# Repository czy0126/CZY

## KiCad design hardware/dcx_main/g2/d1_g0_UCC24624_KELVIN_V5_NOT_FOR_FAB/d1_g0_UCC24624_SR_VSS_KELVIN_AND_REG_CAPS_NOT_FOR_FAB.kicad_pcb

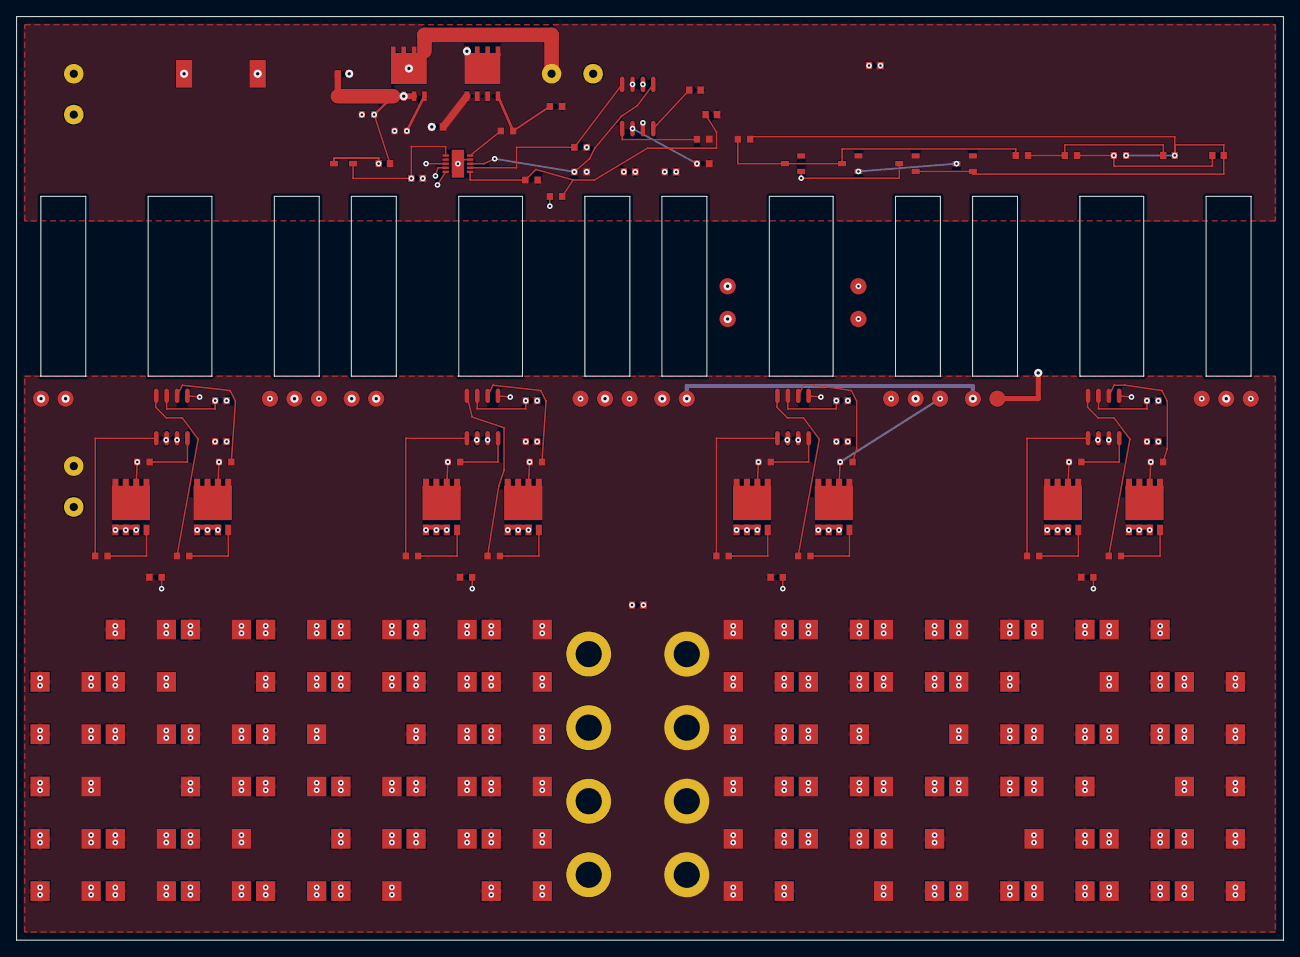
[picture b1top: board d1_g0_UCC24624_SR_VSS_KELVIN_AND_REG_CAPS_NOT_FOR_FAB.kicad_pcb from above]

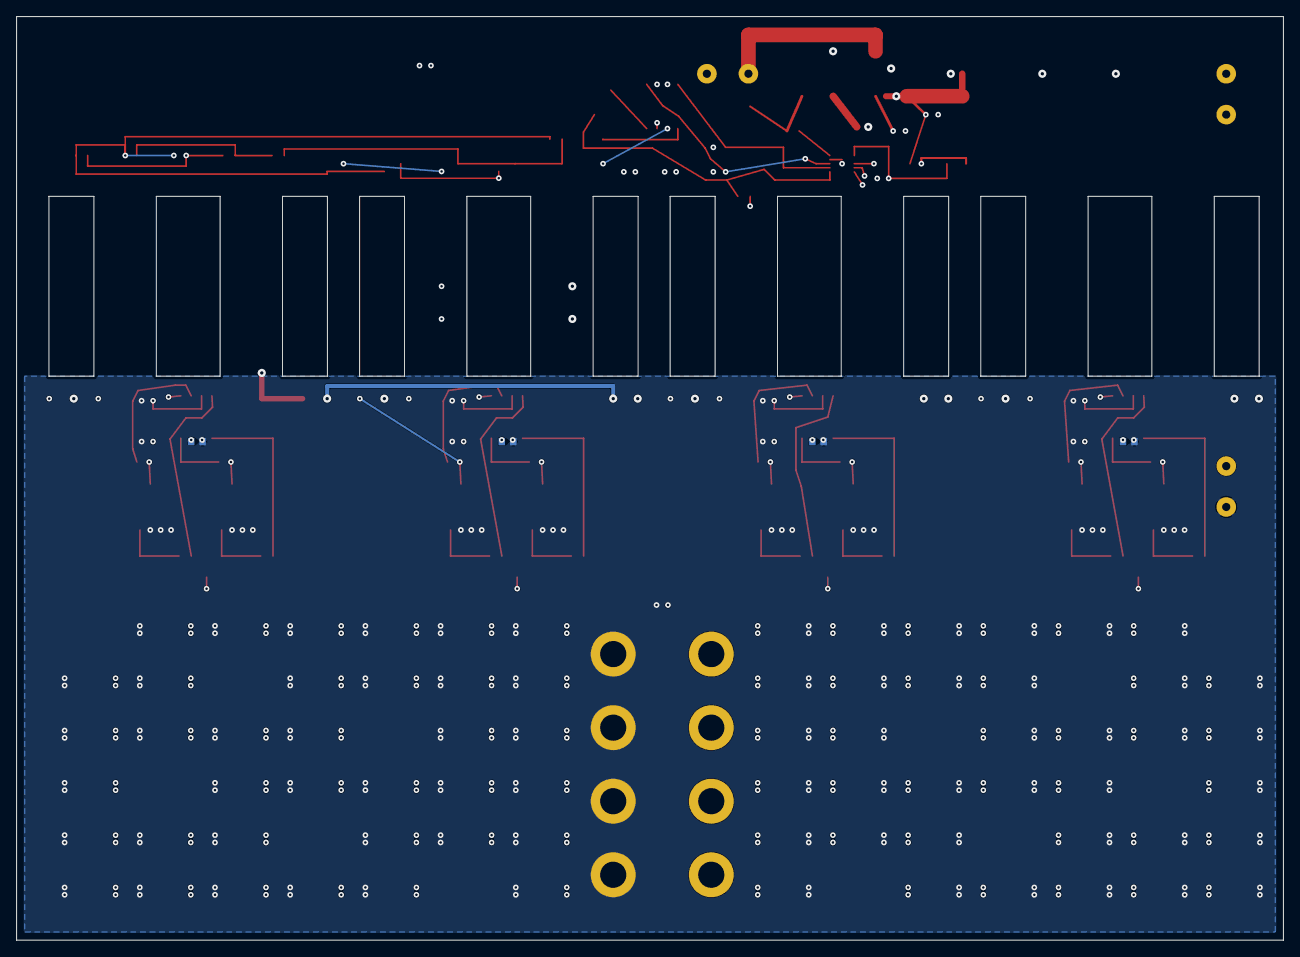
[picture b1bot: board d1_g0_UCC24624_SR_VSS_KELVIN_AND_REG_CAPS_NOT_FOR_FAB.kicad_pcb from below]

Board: 12 copper layers, 155.0 x 113.0 mm, 161 parts (4 on the bottom side), 70 nets.

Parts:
C5, C6, C11, C12, C13, C101, C102, C103, C104, C105, C106, C107, C108, C109, C110, C111, C112: V15_PROVISIONAL_CAD_ONLY
C7, C8, C9, C10: GRM188C71E225KE11_2u2_25V_X7S_DC_BIAS_REVIEW
CHB01, CHB02, CHB03, CHB04, CHB05, CHB06, CHB07, CHB08, CHB09, CHB10, CHB11, CHB12, CHB13, CHB14, CHB15, CHB16, CHB17, CHB18, CHB19, CHB20, CHB21, CHB22, CHB23, CHB24, CHB25, CHB26, CHB27, CHB28, CHB29, CHB30, CHB31, CHB32, CHB33, CHB34, CHB35, CHB36, CHB37, CHB38, CHB39, CHB40, CHB41, CHB42, CHB43, CHB44, CHB45, CHB46, CHB47, CHB48, CHB49, CHB50, CHB51, CHB52, CHB53, CHB54, CHB55, CHB56, CHB57, CHB58, CHB59, CHB60, CHB61, CHB62, CHB63, CHB64, CHB65, CHB66, CHB67, CHB68, CHB69, CHB70, CHB71, CHB72: T530X477M006ATE004; KEMET_T530X_7343_43_OEM_B
CT: LOGICAL_4LAND_CT_NOT_VENDOR_PINOUT
Cin: V15_PROVISIONAL_CAD_ONLY
Cout: V15_PROVISIONAL_CAD_ONLY
Cr: V15_PROVISIONAL_CAD_ONLY
D_BT: V15_PROVISIONAL_CAD_ONLY
D_CT1, D_CT2, D_CT3, D_CT4: V15_PROVISIONAL_CAD_ONLY
J_BIAS_P: PRIMARY_EXTERNAL_12V_NOT_BUILT
J_BIAS_S: SECONDARY_ISOLATED_EXTERNAL_12V_NOT_BUILT
J_IN: V15_PROVISIONAL_CAD_ONLY
J_OUT: EIGHT_PLATED_CONTACTS_VENDOR_UNRATED_NOT_FOR_FAB
Lr: V15_PROVISIONAL_CAD_ONLY
QH: V15_PROVISIONAL_CAD_ONLY
QL: V15_PROVISIONAL_CAD_ONLY
R1, R2, R3, R4, R5, R7, R9, R10, R15, R16, R17, R18, R19, R20, R21, R22, R23, R24, R25, R26, R27, R28, R29, R30, R31, R32, R33, R34, R35: V15_PROVISIONAL_CAD_ONLY
R8: 1k_DNP_UNTIL_EXTERNAL_PERMIT_TESTED
RK1, RK2, RK3, RK4: RC0603JR-070RL_0R_SR_KELVIN_DFM_UNAPPROVED
SR1A, SR1B, SR2A, SR2B, SR3A, SR3B, SR4A, SR4B: V15_PROVISIONAL_CAD_ONLY
T1, T2, T3, T4: LOGICAL_5LAND_NOT_VENDOR_PINOUT_NOT_FOR_FAB
U1, U2, U3, U4, U5, U6: V15_PROVISIONAL_CAD_ONLY

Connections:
CR_CT: CT.PRI_A, Cr.2
CS1: CT.SEC_A, D_CT1.1, D_CT3.3
CS2: CT.SEC_B, D_CT2.1, D_CT4.3
CT_LR: CT.PRI_B, Lr.1
DT: R1.1, U1.1
GA1: R20.2, SR1A.4
GA2: R22.2, SR2A.4
GA3: R24.2, SR3A.4
GA4: R26.2, SR4A.4
GB1: R21.2, SR1B.4
GB2: R23.2, SR2B.4
GB3: R25.2, SR3B.4
GB4: R27.2, SR4B.4
GD1: R9.1, U1.8, U2.7
GD2: R10.1, U1.5, U2.8
GH: QH.4, R4.2, R18.1
GH_DRV: R4.1, U2.4
GL: QL.4, R5.2, R19.1
GL_DRV: R5.1, U2.10
HB: C5.1, D_BT.1, U2.3
OC: C12.1, R16.2, R17.1, U1.3
OC1: C11.1, R15.2, R16.1
OCD: D_CT1.3, D_CT2.3, R3.1, R15.1
OCM: C11.2, C12.2, D_CT3.1, D_CT4.1, R3.2, R17.2
PGND: C6.2, C13.2, C101.2, C102.2, C103.2, C104.2, Cin.2, J_BIAS_P.2, J_IN.2, QL.1, QL.2, QL.3, R1.2, R2.2, R7.2, R9.2, R10.2, R19.2, T4.PRI_B, U1.6, U2.9, U2.11
PRI_12: T1.PRI_B, T2.PRI_A
PRI_23: T2.PRI_B, T3.PRI_A
PRI_34: T3.PRI_B, T4.PRI_A
PRI_T1: Lr.2, T1.PRI_A
REG1: C7.1, U3.3
REG2: C8.1, U4.3
REG3: C9.1, U5.3
REG4: C10.1, U6.3
RT: R2.1, U1.2
RUN: C13.1, R7.1, R8.2, U2.6
SEC1_A: R28.1, SR1A.5, SR1A.6, SR1A.7, SR1A.8, T1.SEC_A
SEC1_B: R29.1, SR1B.5, SR1B.6, SR1B.7, SR1B.8, T1.SEC_B
SEC2_A: R30.1, SR2A.5, SR2A.6, SR2A.7, SR2A.8, T2.SEC_A
SEC2_B: R31.1, SR2B.5, SR2B.6, SR2B.7, SR2B.8, T2.SEC_B
SEC3_A: R32.1, SR3A.5, SR3A.6, SR3A.7, SR3A.8, T3.SEC_A
SEC3_B: R33.1, SR3B.5, SR3B.6, SR3B.7, SR3B.8, T3.SEC_B
SEC4_A: R34.1, SR4A.5, SR4A.6, SR4A.7, SR4A.8, T4.SEC_A
SEC4_B: R35.1, SR4B.5, SR4B.6, SR4B.7, SR4B.8, T4.SEC_B
SR_KELVIN_1: RK1.2, U3.5
SR_KELVIN_2: RK2.2, U4.5
SR_KELVIN_3: RK3.2, U5.5
SR_KELVIN_4: RK4.2, U6.5
SR_SOURCE_RETURN: C7.2, C8.2, C9.2, C10.2, C105.2, C106.2, C107.2, C108.2, C109.2, C110.2, C111.2, C112.2, CHB01.2, CHB02.2, CHB03.2, CHB04.2, CHB05.2, CHB06.2, CHB07.2, CHB08.2, CHB09.2, CHB10.2, CHB11.2, CHB12.2, CHB13.2, CHB14.2, CHB15.2, CHB16.2, CHB17.2, CHB18.2, CHB19.2, CHB20.2, CHB21.2, CHB22.2, CHB23.2, CHB24.2, CHB25.2, CHB26.2, CHB27.2, CHB28.2, CHB29.2, CHB30.2, CHB31.2, CHB32.2, CHB33.2, CHB34.2, CHB35.2, CHB36.2, CHB37.2, CHB38.2, CHB39.2, CHB40.2, CHB41.2, CHB42.2, CHB43.2, CHB44.2, CHB45.2, CHB46.2, CHB47.2, CHB48.2, CHB49.2, CHB50.2, CHB51.2, CHB52.2, CHB53.2, CHB54.2, CHB55.2, CHB56.2, CHB57.2, CHB58.2, CHB59.2, CHB60.2, CHB61.2, CHB62.2, CHB63.2, CHB64.2, CHB65.2, CHB66.2, CHB67.2, CHB68.2, CHB69.2, CHB70.2, CHB71.2, CHB72.2, Cout.2, J_BIAS_S.2, J_OUT.2, RK1.1, RK2.1, RK3.1, RK4.1, SR1A.1, SR1A.2, SR1A.3, SR1B.1, SR1B.2, SR1B.3, SR2A.1, SR2A.2, SR2A.3, SR2B.1, SR2B.2, SR2B.3, SR3A.1, SR3A.2, SR3A.3, SR3B.1, SR3B.2, SR3B.3, SR4A.1, SR4A.2, SR4A.3, SR4B.1, SR4B.2, SR4B.3, U3.2, U4.2, U5.2, U6.2
SS: C6.1, U1.4
SW: C5.2, Cr.1, QH.1, QH.2, QH.3, QL.5, QL.6, QL.7, QL.8, QL.9, R18.2, U2.5
VCC12: C101.1, C102.1, C103.1, C104.1, D_BT.2, J_BIAS_P.1, R8.1, U1.7, U2.1
VCC12_S: C105.1, C106.1, C107.1, C108.1, C109.1, C110.1, C111.1, C112.1, J_BIAS_S.1, U3.7, U4.7, U5.7, U6.7
VD1_A: R28.2, U3.4
VD1_B: R29.2, U3.6
VD2_A: R30.2, U4.4
VD2_B: R31.2, U4.6
VD3_A: R32.2, U5.4
VD3_B: R33.2, U5.6
VD4_A: R34.2, U6.4
VD4_B: R35.2, U6.6
VG1_A: R20.1, U3.1
VG1_B: R21.1, U3.8
VG2_A: R22.1, U4.1
VG2_B: R23.1, U4.8
VG3_A: R24.1, U5.1
VG3_B: R25.1, U5.8
VG4_A: R26.1, U6.1
VG4_B: R27.1, U6.8
VIN_P: Cin.1, J_IN.1, QH.5, QH.6, QH.7, QH.8, QH.9
VOUT: CHB01.1, CHB02.1, CHB03.1, CHB04.1, CHB05.1, CHB06.1, CHB07.1, CHB08.1, CHB09.1, CHB10.1, CHB11.1, CHB12.1, CHB13.1, CHB14.1, CHB15.1, CHB16.1, CHB17.1, CHB18.1, CHB19.1, CHB20.1, CHB21.1, CHB22.1, CHB23.1, CHB24.1, CHB25.1, CHB26.1, CHB27.1, CHB28.1, CHB29.1, CHB30.1, CHB31.1, CHB32.1, CHB33.1, CHB34.1, CHB35.1, CHB36.1, CHB37.1, CHB38.1, CHB39.1, CHB40.1, CHB41.1, CHB42.1, CHB43.1, CHB44.1, CHB45.1, CHB46.1, CHB47.1, CHB48.1, CHB49.1, CHB50.1, CHB51.1, CHB52.1, CHB53.1, CHB54.1, CHB55.1, CHB56.1, CHB57.1, CHB58.1, CHB59.1, CHB60.1, CHB61.1, CHB62.1, CHB63.1, CHB64.1, CHB65.1, CHB66.1, CHB67.1, CHB68.1, CHB69.1, CHB70.1, CHB71.1, CHB72.1, Cout.1, J_OUT.1, T1.CTAP, T2.CTAP, T3.CTAP, T4.CTAP

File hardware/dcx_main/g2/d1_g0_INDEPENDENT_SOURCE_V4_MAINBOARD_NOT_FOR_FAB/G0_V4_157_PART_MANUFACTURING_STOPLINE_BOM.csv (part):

Designator,DesignIntentMPN_VENDOR_UNVERIFIED,DNP,NativeTrialValue,NativePadObjects,NativeRefPinNet,QualifiedPCBFootprint,RealMagneticPinDotSigned
C10,C0603_100n,no,V15_PROVISIONAL_CAD_ONLY,2,1=REG4;2=SR_SOURCE_RETURN,no,no
C101,C0603_100n (design value from peripheral register; OEM not qualified),no,V15_PROVISIONAL_CAD_ONLY,2,1=VCC12;2=PGND,no,no
C102,C0603_100n (design value from peripheral register; OEM not qualified),no,V15_PROVISIONAL_CAD_ONLY,2,1=VCC12;2=PGND,no,no
C103,C0603_100n (design value from peripheral register; OEM not qualified),no,V15_PROVISIONAL_CAD_ONLY,2,1=VCC12;2=PGND,no,no
C104,C0603_100n (design value from peripheral register; OEM not qualified),no,V15_PROVISIONAL_CAD_ONLY,2,1=VCC12;2=PGND,no,no
C105,C0603_100n (design value from peripheral register; OEM not qualified),no,V15_PROVISIONAL_CAD_ONLY,2,1=VCC12_S;2=SR_SOURCE_RETURN,no,no
C106,C0603_100n (design value from peripheral register; OEM not qualified),no,V15_PROVISIONAL_CAD_ONLY,2,1=VCC12_S;2=SR_SOURCE_RETURN,no,no
C107,C0603_100n (design value from peripheral register; OEM not qualified),no,V15_PROVISIONAL_CAD_ONLY,2,1=VCC12_S;2=SR_SOURCE_RETURN,no,no
C108,C0603_100n (design value from peripheral register; OEM not qualified),no,V15_PROVISIONAL_CAD_ONLY,2,1=VCC12_S;2=SR_SOURCE_RETURN,no,no
C109,C0603_100n (design value from peripheral register; OEM not qualified),no,V15_PROVISIONAL_CAD_ONLY,2,1=VCC12_S;2=SR_SOURCE_RETURN,no,no
C11,C0603_100n,no,V15_PROVISIONAL_CAD_ONLY,2,1=OC1;2=OCM,no,no
C110,C0603_100n (design value from peripheral register; OEM not qualified),no,V15_PROVISIONAL_CAD_ONLY,2,1=VCC12_S;2=SR_SOURCE_RETURN,no,no
C111,C0603_100n (design value from peripheral register; OEM not qualified),no,V15_PROVISIONAL_CAD_ONLY,2,1=VCC12_S;2=SR_SOURCE_RETURN,no,no
C112,C0603_100n (design value from peripheral register; OEM not qualified),no,V15_PROVISIONAL_CAD_ONLY,2,1=VCC12_S;2=SR_SOURCE_RETURN,no,no
C12,C0603_100n,no,V15_PROVISIONAL_CAD_ONLY,2,1=OC;2=OCM,no,no
C13,C0603_100n (design value from peripheral register; OEM not qualified),no,V15_PROVISIONAL_CAD_ONLY,2,1=RUN;2=PGND,no,no
C5,C0603_100n,no,V15_PROVISIONAL_CAD_ONLY,2,1=HB;2=SW,no,no
C6,C0603_100n,no,V15_PROVISIONAL_CAD_ONLY,2,1=SS;2=PGND,no,no
C7,C0603_100n,no,V15_PROVISIONAL_CAD_ONLY,2,1=REG1;2=SR_SOURCE_RETURN,no,no
C8,C0603_100n,no,V15_PROVISIONAL_CAD_ONLY,2,1=REG2;2=SR_SOURCE_RETURN,no,no
C9,C0603_100n,no,V15_PROVISIONAL_CAD_ONLY,2,1=REG3;2=SR_SOURCE_RETURN,no,no
CHB01,"T530 OEM tentative, MPN and derating require signoff",no,T530X477M006ATE004,2,1=VOUT;2=SR_SOURCE_RETURN,no,no
CHB02,"T530 OEM tentative, MPN and derating require signoff",no,T530X477M006ATE004,2,1=VOUT;2=SR_SOURCE_RETURN,no,no
CHB03,"T530 OEM tentative, MPN and derating require signoff",no,T530X477M006ATE004,2,1=VOUT;2=SR_SOURCE_RETURN,no,no
CHB04,"T530 OEM tentative, MPN and derating require signoff",no,T530X477M006ATE004,2,1=VOUT;2=SR_SOURCE_RETURN,no,no
CHB05,"T530 OEM tentative, MPN and derating require signoff",no,T530X477M006ATE004,2,1=VOUT;2=SR_SOURCE_RETURN,no,no
CHB06,"T530 OEM tentative, MPN and derating require signoff",no,T530X477M006ATE004,2,1=VOUT;2=SR_SOURCE_RETURN,no,no
CHB07,"T530 OEM tentative, MPN and derating require signoff",no,T530X477M006ATE004,2,1=VOUT;2=SR_SOURCE_RETURN,no,no
CHB08,"T530 OEM tentative, MPN and derating require signoff",no,T530X477M006ATE004,2,1=VOUT;2=SR_SOURCE_RETURN,no,no
CHB09,"T530 OEM tentative, MPN and derating require signoff",no,T530X477M006ATE004,2,1=VOUT;2=SR_SOURCE_RETURN,no,no
CHB10,"T530 OEM tentative, MPN and derating require signoff",no,T530X477M006ATE004,2,1=VOUT;2=SR_SOURCE_RETURN,no,no
CHB11,"T530 OEM tentative, MPN and derating require signoff",no,T530X477M006ATE004,2,1=VOUT;2=SR_SOURCE_RETURN,no,no
CHB12,"T530 OEM tentative, MPN and derating require signoff",no,T530X477M006ATE004,2,1=VOUT;2=SR_SOURCE_RETURN,no,no
CHB13,"T530 OEM tentative, MPN and derating require signoff",no,T530X477M006ATE004,2,1=VOUT;2=SR_SOURCE_RETURN,no,no
CHB14,"T530 OEM tentative, MPN and derating require signoff",no,T530X477M006ATE004,2,1=VOUT;2=SR_SOURCE_RETURN,no,no
CHB15,"T530 OEM tentative, MPN and derating require signoff",no,T530X477M006ATE004,2,1=VOUT;2=SR_SOURCE_RETURN,no,no
CHB16,"T530 OEM tentative, MPN and derating require signoff",no,T530X477M006ATE004,2,1=VOUT;2=SR_SOURCE_RETURN,no,no
CHB17,"T530 OEM tentative, MPN and derating require signoff",no,T530X477M006ATE004,2,1=VOUT;2=SR_SOURCE_RETURN,no,no
CHB18,"T530 OEM tentative, MPN and derating require signoff",no,T530X477M006ATE004,2,1=VOUT;2=SR_SOURCE_RETURN,no,no
CHB19,"T530 OEM tentative, MPN and derating require signoff",no,T530X477M006ATE004,2,1=VOUT;2=SR_SOURCE_RETURN,no,no
CHB20,"T530 OEM tentative, MPN and derating require signoff",no,T530X477M006ATE004,2,1=VOUT;2=SR_SOURCE_RETURN,no,no
CHB21,"T530 OEM tentative, MPN and derating require signoff",no,T530X477M006ATE004,2,1=VOUT;2=SR_SOURCE_RETURN,no,no
CHB22,"T530 OEM tentative, MPN and derating require signoff",no,T530X477M006ATE004,2,1=VOUT;2=SR_SOURCE_RETURN,no,no
CHB23,"T530 OEM tentative, MPN and derating require signoff",no,T530X477M006ATE004,2,1=VOUT;2=SR_SOURCE_RETURN,no,no
CHB24,"T530 OEM tentative, MPN and derating require signoff",no,T530X477M006ATE004,2,1=VOUT;2=SR_SOURCE_RETURN,no,no
CHB25,"T530 OEM tentative, MPN and derating require signoff",no,T530X477M006ATE004,2,1=VOUT;2=SR_SOURCE_RETURN,no,no
CHB26,"T530 OEM tentative, MPN and derating require signoff",no,T530X477M006ATE004,2,1=VOUT;2=SR_SOURCE_RETURN,no,no
CHB27,"T530 OEM tentative, MPN and derating require signoff",no,T530X477M006ATE004,2,1=VOUT;2=SR_SOURCE_RETURN,no,no
CHB28,"T530 OEM tentative, MPN and derating require signoff",no,T530X477M006ATE004,2,1=VOUT;2=SR_SOURCE_RETURN,no,no
CHB29,"T530 OEM tentative, MPN and derating require signoff",no,T530X477M006ATE004,2,1=VOUT;2=SR_SOURCE_RETURN,no,no
CHB30,"T530 OEM tentative, MPN and derating require signoff",no,T530X477M006ATE004,2,1=VOUT;2=SR_SOURCE_RETURN,no,no
CHB31,"T530 OEM tentative, MPN and derating require signoff",no,T530X477M006ATE004,2,1=VOUT;2=SR_SOURCE_RETURN,no,no
CHB32,"T530 OEM tentative, MPN and derating require signoff",no,T530X477M006ATE004,2,1=VOUT;2=SR_SOURCE_RETURN,no,no
CHB33,"T530 OEM tentative, MPN and derating require signoff",no,T530X477M006ATE004,2,1=VOUT;2=SR_SOURCE_RETURN,no,no
CHB34,"T530 OEM tentative, MPN and derating require signoff",no,T530X477M006ATE004,2,1=VOUT;2=SR_SOURCE_RETURN,no,no
CHB35,"T530 OEM tentative, MPN and derating require signoff",no,T530X477M006ATE004,2,1=VOUT;2=SR_SOURCE_RETURN,no,no
CHB36,"T530 OEM tentative, MPN and derating require signoff",no,T530X477M006ATE004,2,1=VOUT;2=SR_SOURCE_RETURN,no,no
CHB37,"T530 OEM tentative, MPN and derating require signoff",no,T530X477M006ATE004,2,1=VOUT;2=SR_SOURCE_RETURN,no,no
CHB38,"T530 OEM tentative, MPN and derating require signoff",no,T530X477M006ATE004,2,1=VOUT;2=SR_SOURCE_RETURN,no,no
CHB39,"T530 OEM tentative, MPN and derating require signoff",no,T530X477M006ATE004,2,1=VOUT;2=SR_SOURCE_RETURN,no,no
CHB40,"T530 OEM tentative, MPN and derating require signoff",no,T530X477M006ATE004,2,1=VOUT;2=SR_SOURCE_RETURN,no,no
CHB41,"T530 OEM tentative, MPN and derating require signoff",no,T530X477M006ATE004,2,1=VOUT;2=SR_SOURCE_RETURN,no,no
CHB42,"T530 OEM tentative, MPN and derating require signoff",no,T530X477M006ATE004,2,1=VOUT;2=SR_SOURCE_RETURN,no,no
CHB43,"T530 OEM tentative, MPN and derating require signoff",no,T530X477M006ATE004,2,1=VOUT;2=SR_SOURCE_RETURN,no,no
CHB44,"T530 OEM tentative, MPN and derating require signoff",no,T530X477M006ATE004,2,1=VOUT;2=SR_SOURCE_RETURN,no,no
CHB45,"T530 OEM tentative, MPN and derating require signoff",no,T530X477M006ATE004,2,1=VOUT;2=SR_SOURCE_RETURN,no,no
CHB46,"T530 OEM tentative, MPN and derating require signoff",no,T530X477M006ATE004,2,1=VOUT;2=SR_SOURCE_RETURN,no,no
CHB47,"T530 OEM tentative, MPN and derating require signoff",no,T530X477M006ATE004,2,1=VOUT;2=SR_SOURCE_RETURN,no,no
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
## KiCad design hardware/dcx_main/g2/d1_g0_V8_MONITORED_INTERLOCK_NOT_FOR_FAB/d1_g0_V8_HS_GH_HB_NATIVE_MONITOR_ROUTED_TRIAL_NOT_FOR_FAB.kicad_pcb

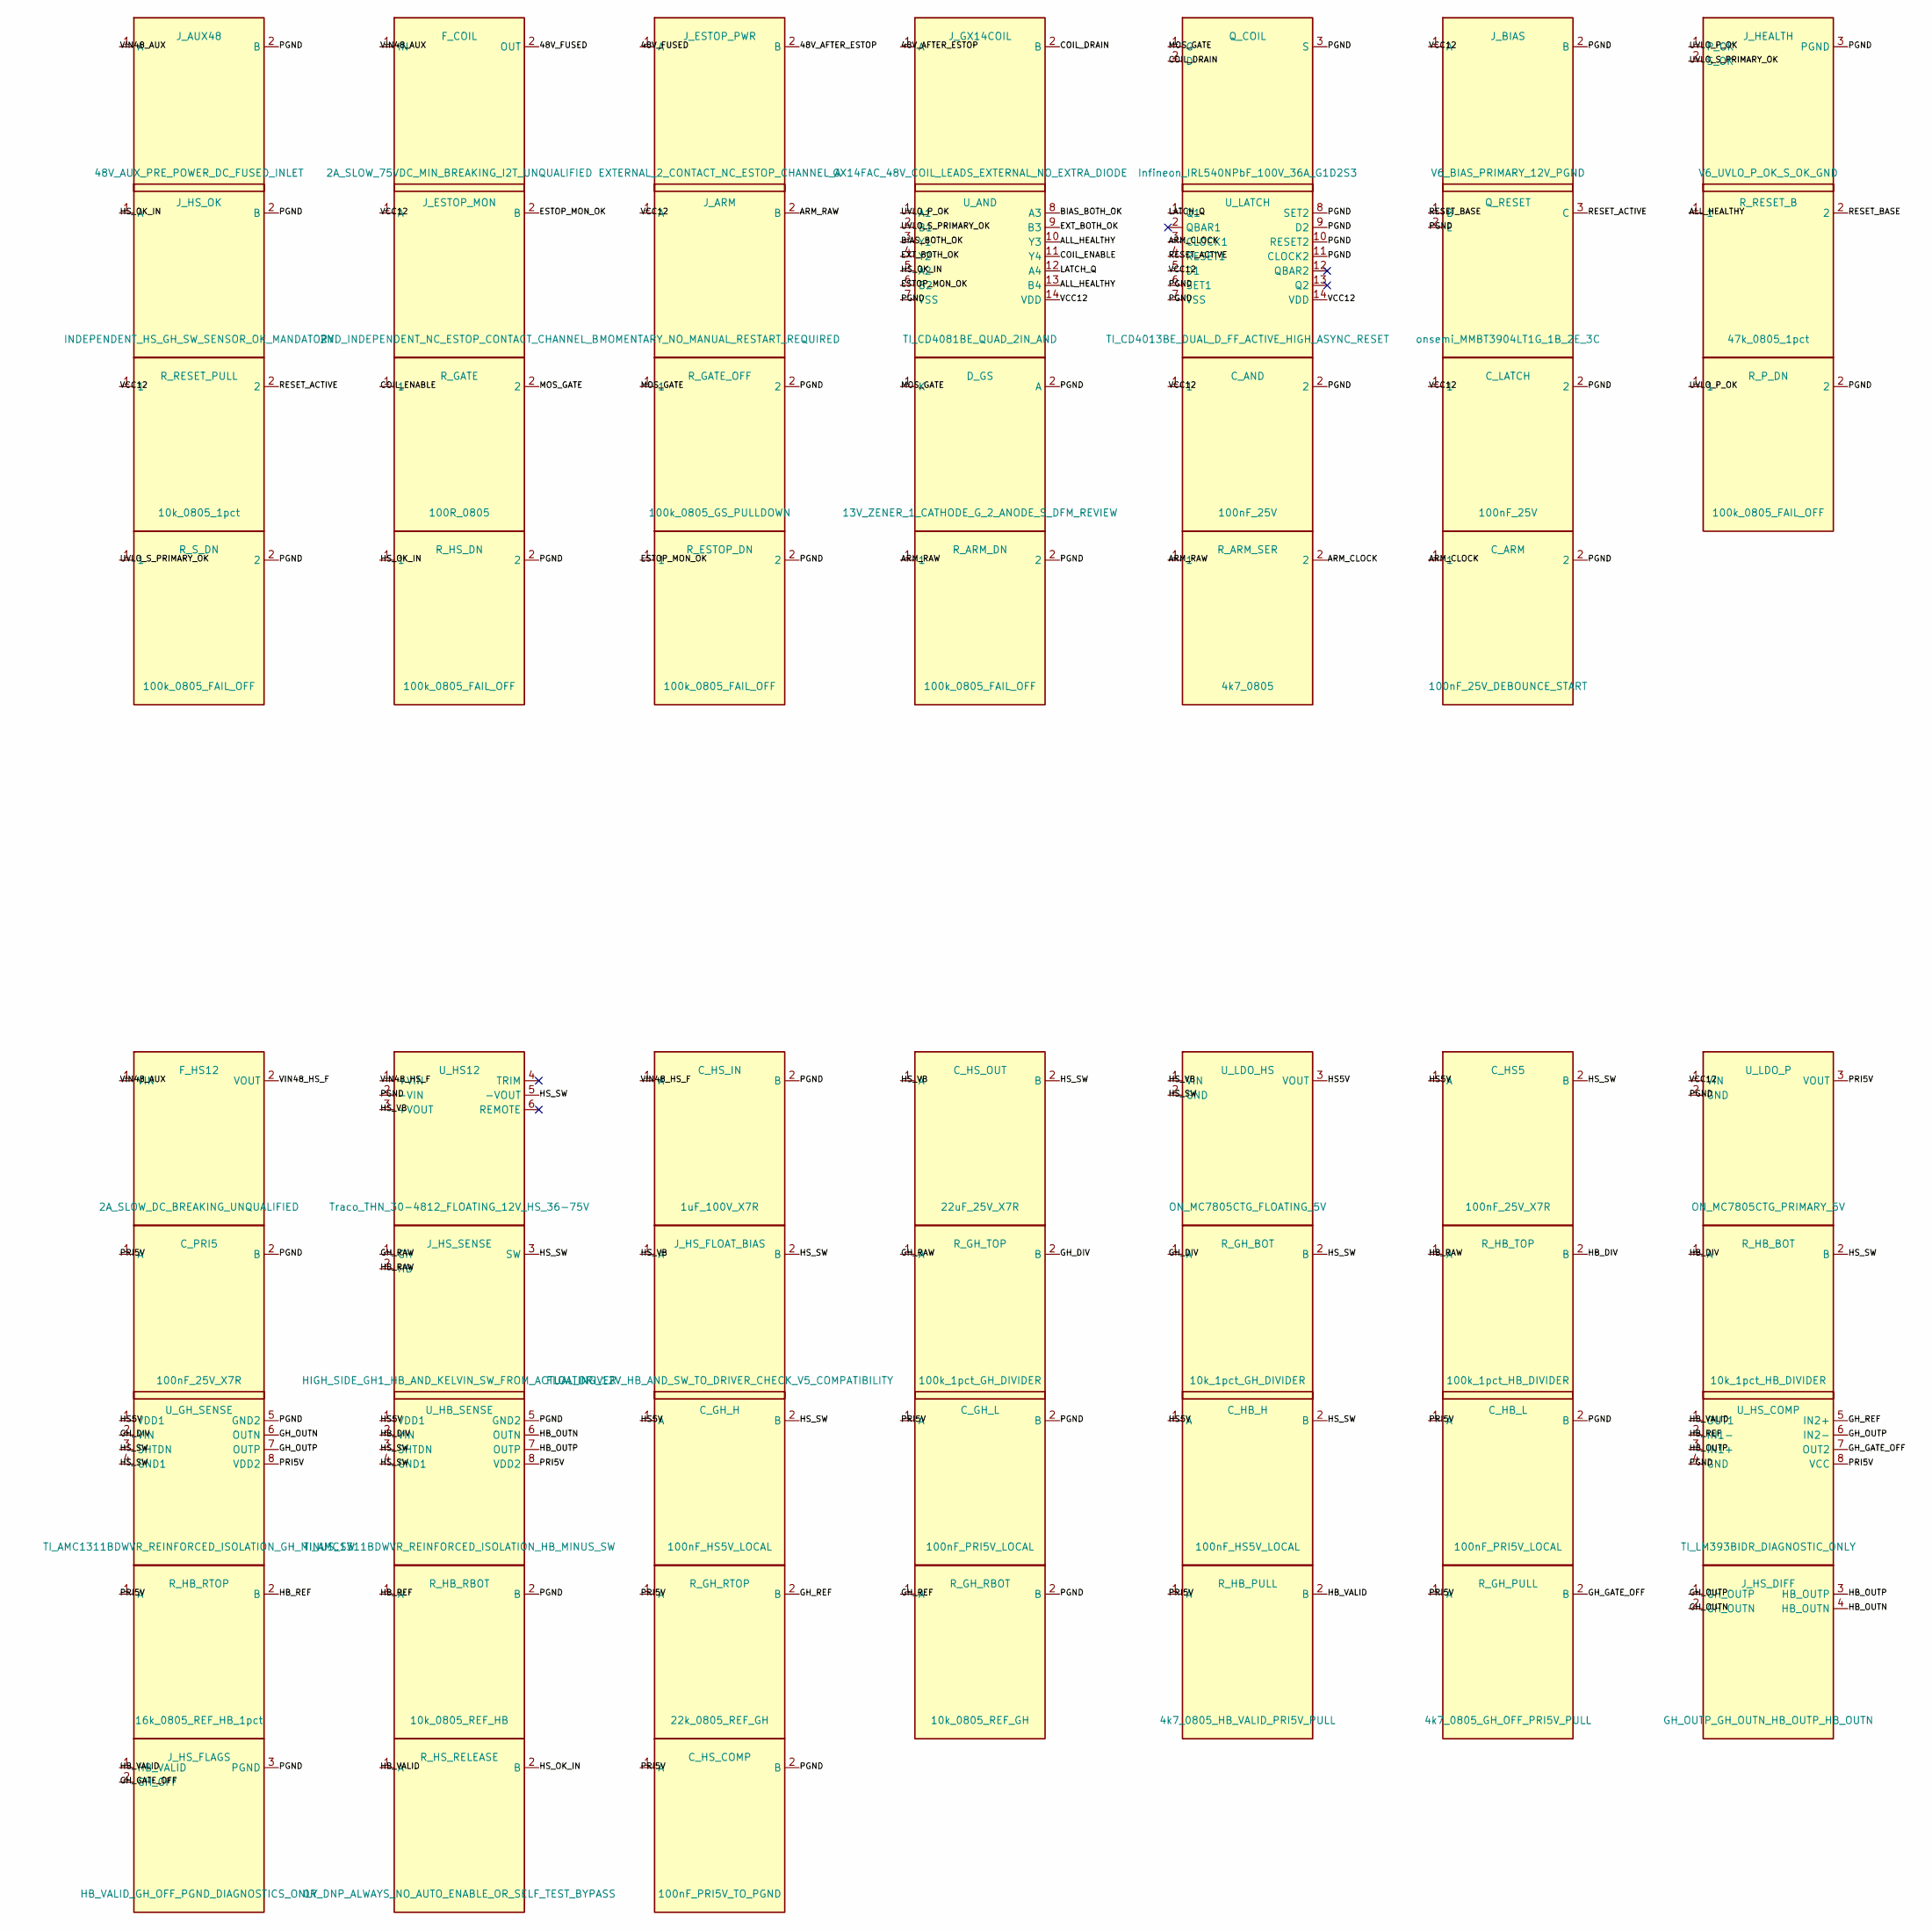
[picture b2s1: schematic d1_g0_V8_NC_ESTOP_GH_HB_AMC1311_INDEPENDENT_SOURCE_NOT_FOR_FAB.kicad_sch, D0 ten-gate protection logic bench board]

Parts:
C_AND: 100nF_25V; C_0603_1608Metric
C_ARM: 100nF_25V_DEBOUNCE_START; C_0603_1608Metric
C_GH_H: 100nF_HS5V_LOCAL; C_0603_1608Metric
C_GH_L: 100nF_PRI5V_LOCAL; C_0603_1608Metric
C_HB_H: 100nF_HS5V_LOCAL; C_0603_1608Metric
C_HB_L: 100nF_PRI5V_LOCAL; C_0603_1608Metric
C_HS5: 100nF_25V_X7R; C_0603_1608Metric
C_HS_COMP: 100nF_PRI5V_TO_PGND; C_0603_1608Metric
C_HS_IN: 1uF_100V_X7R; C_1206_3216Metric
C_HS_OUT: 22uF_25V_X7R; C_1210_3225Metric
C_LATCH: 100nF_25V; C_0603_1608Metric
C_PRI5: 100nF_25V_X7R; C_0603_1608Metric
D_GS: 13V_ZENER_1_CATHODE_G_2_ANODE_S_DFM_REVIEW; D_SOD-123
F_COIL: 2A_SLOW_75VDC_MIN_BREAKING_I2T_UNQUALIFIED; Fuse_1812_4532Metric
F_HS12: 2A_SLOW_DC_BREAKING_UNQUALIFIED; Fuse_1812_4532Metric
J_ARM: MOMENTARY_NO_MANUAL_RESTART_REQUIRED; TerminalBlock_MaiXu_MX126-5.0-02P_1x02_P5.00mm
J_AUX48: 48V_AUX_PRE_POWER_DC_FUSED_INLET; TerminalBlock_MaiXu_MX126-5.0-02P_1x02_P5.00mm
J_BIAS: V6_BIAS_PRIMARY_12V_PGND; TerminalBlock_MaiXu_MX126-5.0-02P_1x02_P5.00mm
J_ESTOP_MON: 2ND_INDEPENDENT_NC_ESTOP_CONTACT_CHANNEL_B; TerminalBlock_MaiXu_MX126-5.0-02P_1x02_P5.00mm
J_ESTOP_PWR: EXTERNAL_2_CONTACT_NC_ESTOP_CHANNEL_A; TerminalBlock_MaiXu_MX126-5.0-02P_1x02_P5.00mm
J_GX14COIL: GX14FAC_48V_COIL_LEADS_EXTERNAL_NO_EXTRA_DIODE; TerminalBlock_MaiXu_MX126-5.0-02P_1x02_P5.00mm
J_HEALTH: V6_UVLO_P_OK_S_OK_GND; PinHeader_1x03_P2.54mm_Vertical
J_HS_DIFF: GH_OUTP_GH_OUTN_HB_OUTP_HB_OUTN; PinHeader_1x04_P2.54mm_Vertical
J_HS_FLAGS: HB_VALID_GH_OFF_PGND_DIAGNOSTICS_ONLY; PinHeader_1x03_P2.54mm_Vertical
J_HS_FLOAT_BIAS: FLOATING_12V_HB_AND_SW_TO_DRIVER_CHECK_V5_COMPATI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; TerminalBlock_MaiXu_MX126-5.0-02P_1x02_P5.00mm
J_HS_OK: INDEPENDENT_HS_GH_SW_SENSOR_OK_MANDATORY; TerminalBlock_MaiXu_MX126-5.0-02P_1x02_P5.00mm
J_HS_SENSE: HIGH_SIDE_GH1_HB_AND_KELVIN_SW_FROM_ACTUAL_DRIVER; TerminalBlock_MaiXu_MX126-5.0-03P_1x03_P5.00mm
Q_COIL: Infineon_IRL540NPbF_100V_36A_G1D2S3; TO-220-3_Vertical
Q_RESET: onsemi_MMBT3904LT1G_1B_2E_3C; SOT-23
R_ARM_DN: 100k_0805_FAIL_OFF; R_0805_2012Metric
R_ARM_SER: 4k7_0805; R_0805_2012Metric
R_ESTOP_DN: 100k_0805_FAIL_OFF; R_0805_2012Metric
R_GATE: 100R_0805; R_0805_2012Metric
R_GATE_OFF: 100k_0805_GS_PULLDOWN; R_0805_2012Metric
R_GH_BOT: 10k_1pct_GH_DIVIDER; R_0805_2012Metric
R_GH_PULL: 4k7_0805_GH_OFF_PRI5V_PULL; R_0805_2012Metric
R_GH_RBOT: 10k_0805_REF_GH; R_0805_2012Metric
R_GH_RTOP: 22k_0805_REF_GH; R_0805_2012Metric
R_GH_TOP: 100k_1pct_GH_DIVIDER; R_0805_2012Metric
R_HB_BOT: 10k_1pct_HB_DIVIDER; R_0805_2012Metric
R_HB_PULL: 4k7_0805_HB_VALID_PRI5V_PULL; R_0805_2012Metric
R_HB_RBOT: 10k_0805_REF_HB; R_0805_2012Metric
R_HB_RTOP: 16k_0805_REF_HB_1pct; R_0805_2012Metric
R_HB_TOP: 100k_1pct_HB_DIVIDER; R_0805_2012Metric
R_HS_DN: 100k_0805_FAIL_OFF; R_0805_2012Metric
R_HS_RELEASE: 0R_DNP_ALWAYS_NO_AUTO_ENABLE_OR_SELF_TEST_BYPASS; R_0805_2012Metric
R_P_DN: 100k_0805_FAIL_OFF; R_0805_2012Metric
R_RESET_B: 47k_0805_1pct; R_0805_2012Metric
R_RESET_PULL: 10k_0805_1pct; R_0805_2012Metric
R_S_DN: 100k_0805_FAIL_OFF; R_0805_2012Metric
U_AND: TI_CD4081BE_QUAD_2IN_AND; DIP-14_W7.62mm
U_GH_SENSE: TI_AMC1311BDWVR_REINFORCED_ISOLATION_GH_MINUS_SW; SOIC-8_7.5x5.85mm_P1.27mm
U_HB_SENSE: TI_AMC1311BDWVR_REINFORCED_ISOLATION_HB_MINUS_SW; SOIC-8_7.5x5.85mm_P1.27mm
U_HS12: Traco_THN_30-4812_FLOATING_12V_HS_36-75V; Converter_DCDC_TRACO_THN30-xxxx_THT
U_HS_COMP: TI_LM393BIDR_DIAGNOSTIC_ONLY; SOIC-8_3.9x4.9mm_P1.27mm
U_LATCH: TI_CD4013BE_DUAL_D_FF_ACTIVE_HIGH_ASYNC_RESET; DIP-14_W7.62mm
U_LDO_HS: ON_MC7805CTG_FLOATING_5V; TO-220-3_Vertical
U_LDO_P: ON_MC7805CTG_PRIMARY_5V; TO-220-3_Vertical

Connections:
48V_AFTER_ESTOP: J_ESTOP_PWR.2 (B), J_GX14COIL.1 (A)
48V_FUSED: F_COIL.2 (OUT), J_ESTOP_PWR.1 (A)
ALL_HEALTHY: R_RESET_B.1, U_AND.10 (Y3), U_AND.13 (B4)
ARM_CLOCK: C_ARM.1, R_ARM_SER.2, U_LATCH.3 (CLOCK1)
ARM_RAW: J_ARM.2 (B), R_ARM_DN.1, R_ARM_SER.1
BIAS_BOTH_OK: U_AND.3 (Y1), U_AND.8 (A3)
COIL_DRAIN: J_GX14COIL.2 (B), Q_COIL.2 (D)
COIL_ENABLE: R_GATE.1, U_AND.11 (Y4)
ESTOP_MON_OK: J_ESTOP_MON.2 (B), R_ESTOP_DN.1, U_AND.6 (B2)
EXT_BOTH_OK: U_AND.4 (Y2), U_AND.9 (B3)
GH_DIV: R_GH_BOT.1 (A), R_GH_TOP.2 (B), U_GH_SENSE.2 (VIN)
GH_GATE_OFF: J_HS_FLAGS.2 (GH_OFF), R_GH_PULL.2 (B), U_HS_COMP.7 (OUT2)
GH_OUTN: J_HS_DIFF.2 (GH_OUTN), U_GH_SENSE.6 (OUTN)
GH_OUTP: J_HS_DIFF.1 (GH_OUTP), U_GH_SENSE.7 (OUTP), U_HS_COMP.6 (IN2-)
GH_RAW: J_HS_SENSE.1 (GH), R_GH_TOP.1 (A)
GH_REF: R_GH_RBOT.1 (A), R_GH_RTOP.2 (B), U_HS_COMP.5 (IN2+)
HB_DIV: R_HB_BOT.1 (A), R_HB_TOP.2 (B), U_HB_SENSE.2 (VIN)
HB_OUTN: J_HS_DIFF.4 (HB_OUTN), U_HB_SENSE.6 (OUTN)
HB_OUTP: J_HS_DIFF.3 (HB_OUTP), U_HB_SENSE.7 (OUTP), U_HS_COMP.3 (IN1+)
HB_RAW: J_HS_SENSE.2 (HB), R_HB_TOP.1 (A)
HB_REF: R_HB_RBOT.1 (A), R_HB_RTOP.2 (B), U_HS_COMP.2 (IN1-)
HB_VALID: J_HS_FLAGS.1 (HB_VALID), R_HB_PULL.2 (B), R_HS_RELEASE.1 (A), U_HS_COMP.1 (OUT1)
HS5V: C_GH_H.1 (A), C_HB_H.1 (A), C_HS5.1 (A), U_GH_SENSE.1 (VDD1), U_HB_SENSE.1 (VDD1), U_LDO_HS.3 (VOUT)
HS_OK_IN: J_HS_OK.1 (A), R_HS_DN.1, R_HS_RELEASE.2 (B), U_AND.5 (A2)
HS_SW: C_GH_H.2 (B), C_HB_H.2 (B), C_HS5.2 (B), C_HS_OUT.2 (B), J_HS_FLOAT_BIAS.2 (B), J_HS_SENSE.3 (SW), R_GH_BOT.2 (B), R_HB_BOT.2 (B), U_GH_SENSE.3 (SHTDN), U_GH_SENSE.4 (GND1), U_HB_SENSE.3 (SHTDN), U_HB_SENSE.4 (GND1), U_HS12.5 (-VOUT), U_LDO_HS.2 (GND)
HS_VB: C_HS_OUT.1 (A), J_HS_FLOAT_BIAS.1 (A), U_HS12.3 (+VOUT), U_LDO_HS.1 (VIN)
LATCH_Q: U_AND.12 (A4), U_LATCH.1 (Q1)
MOS_GATE: D_GS.1 (K), Q_COIL.1 (G), R_GATE.2, R_GATE_OFF.1
PGND: C_AND.2, C_ARM.2, C_GH_L.2 (B), C_HB_L.2 (B), C_HS_COMP.2 (B), C_HS_IN.2 (B), C_LATCH.2, C_PRI5.2 (B), D_GS.2 (A), J_AUX48.2 (B), J_BIAS.2 (B), J_HEALTH.3 (PGND), J_HS_FLAGS.3 (PGND), J_HS_OK.2 (B), Q_COIL.3 (S), Q_RESET.2 (E), R_ARM_DN.2, R_ESTOP_DN.2, R_GATE_OFF.2, R_GH_RBOT.2 (B), R_HB_RBOT.2 (B), R_HS_DN.2, R_P_DN.2, R_S_DN.2, U_AND.7 (VSS), U_GH_SENSE.5 (GND2), U_HB_SENSE.5 (GND2), U_HS12.2 (-VIN), U_HS_COMP.4 (GND), U_LATCH.6 (SET1), U_LATCH.7 (VSS), U_LATCH.8 (SET2), U_LATCH.9 (D2), U_LATCH.10 (RESET2), U_LATCH.11 (CLOCK2), U_LDO_P.2 (GND)
PRI5V: C_GH_L.1 (A), C_HB_L.1 (A), C_HS_COMP.1 (A), C_PRI5.1 (A), R_GH_PULL.1 (A), R_GH_RTOP.1 (A), R_HB_PULL.1 (A), R_HB_RTOP.1 (A), U_GH_SENSE.8 (VDD2), U_HB_SENSE.8 (VDD2), U_HS_COMP.8 (VCC), U_LDO_P.3 (VOUT)
RESET_ACTIVE: Q_RESET.3 (C), R_RESET_PULL.2, U_LATCH.4 (RESET1)
RESET_BASE: Q_RESET.1 (B), R_RESET_B.2
UVLO_P_OK: J_HEALTH.1 (P_OK), R_P_DN.1, U_AND.1 (A1)
UVLO_S_PRIMARY_OK: J_HEALTH.2 (S_OK), R_S_DN.1, U_AND.2 (B1)
VCC12: C_AND.1, C_LATCH.1, J_ARM.1 (A), J_BIAS.1 (A), J_ESTOP_MON.1 (A), R_RESET_PULL.1, U_AND.14 (VDD), U_LATCH.5 (D1), U_LATCH.14 (VDD), U_LDO_P.1 (VIN)
VIN48_AUX: F_COIL.1 (IN), F_HS12.1 (VIN), J_AUX48.1 (A)
VIN48_HS_F: C_HS_IN.1 (A), F_HS12.2 (VOUT), U_HS12.1 (+VIN)
